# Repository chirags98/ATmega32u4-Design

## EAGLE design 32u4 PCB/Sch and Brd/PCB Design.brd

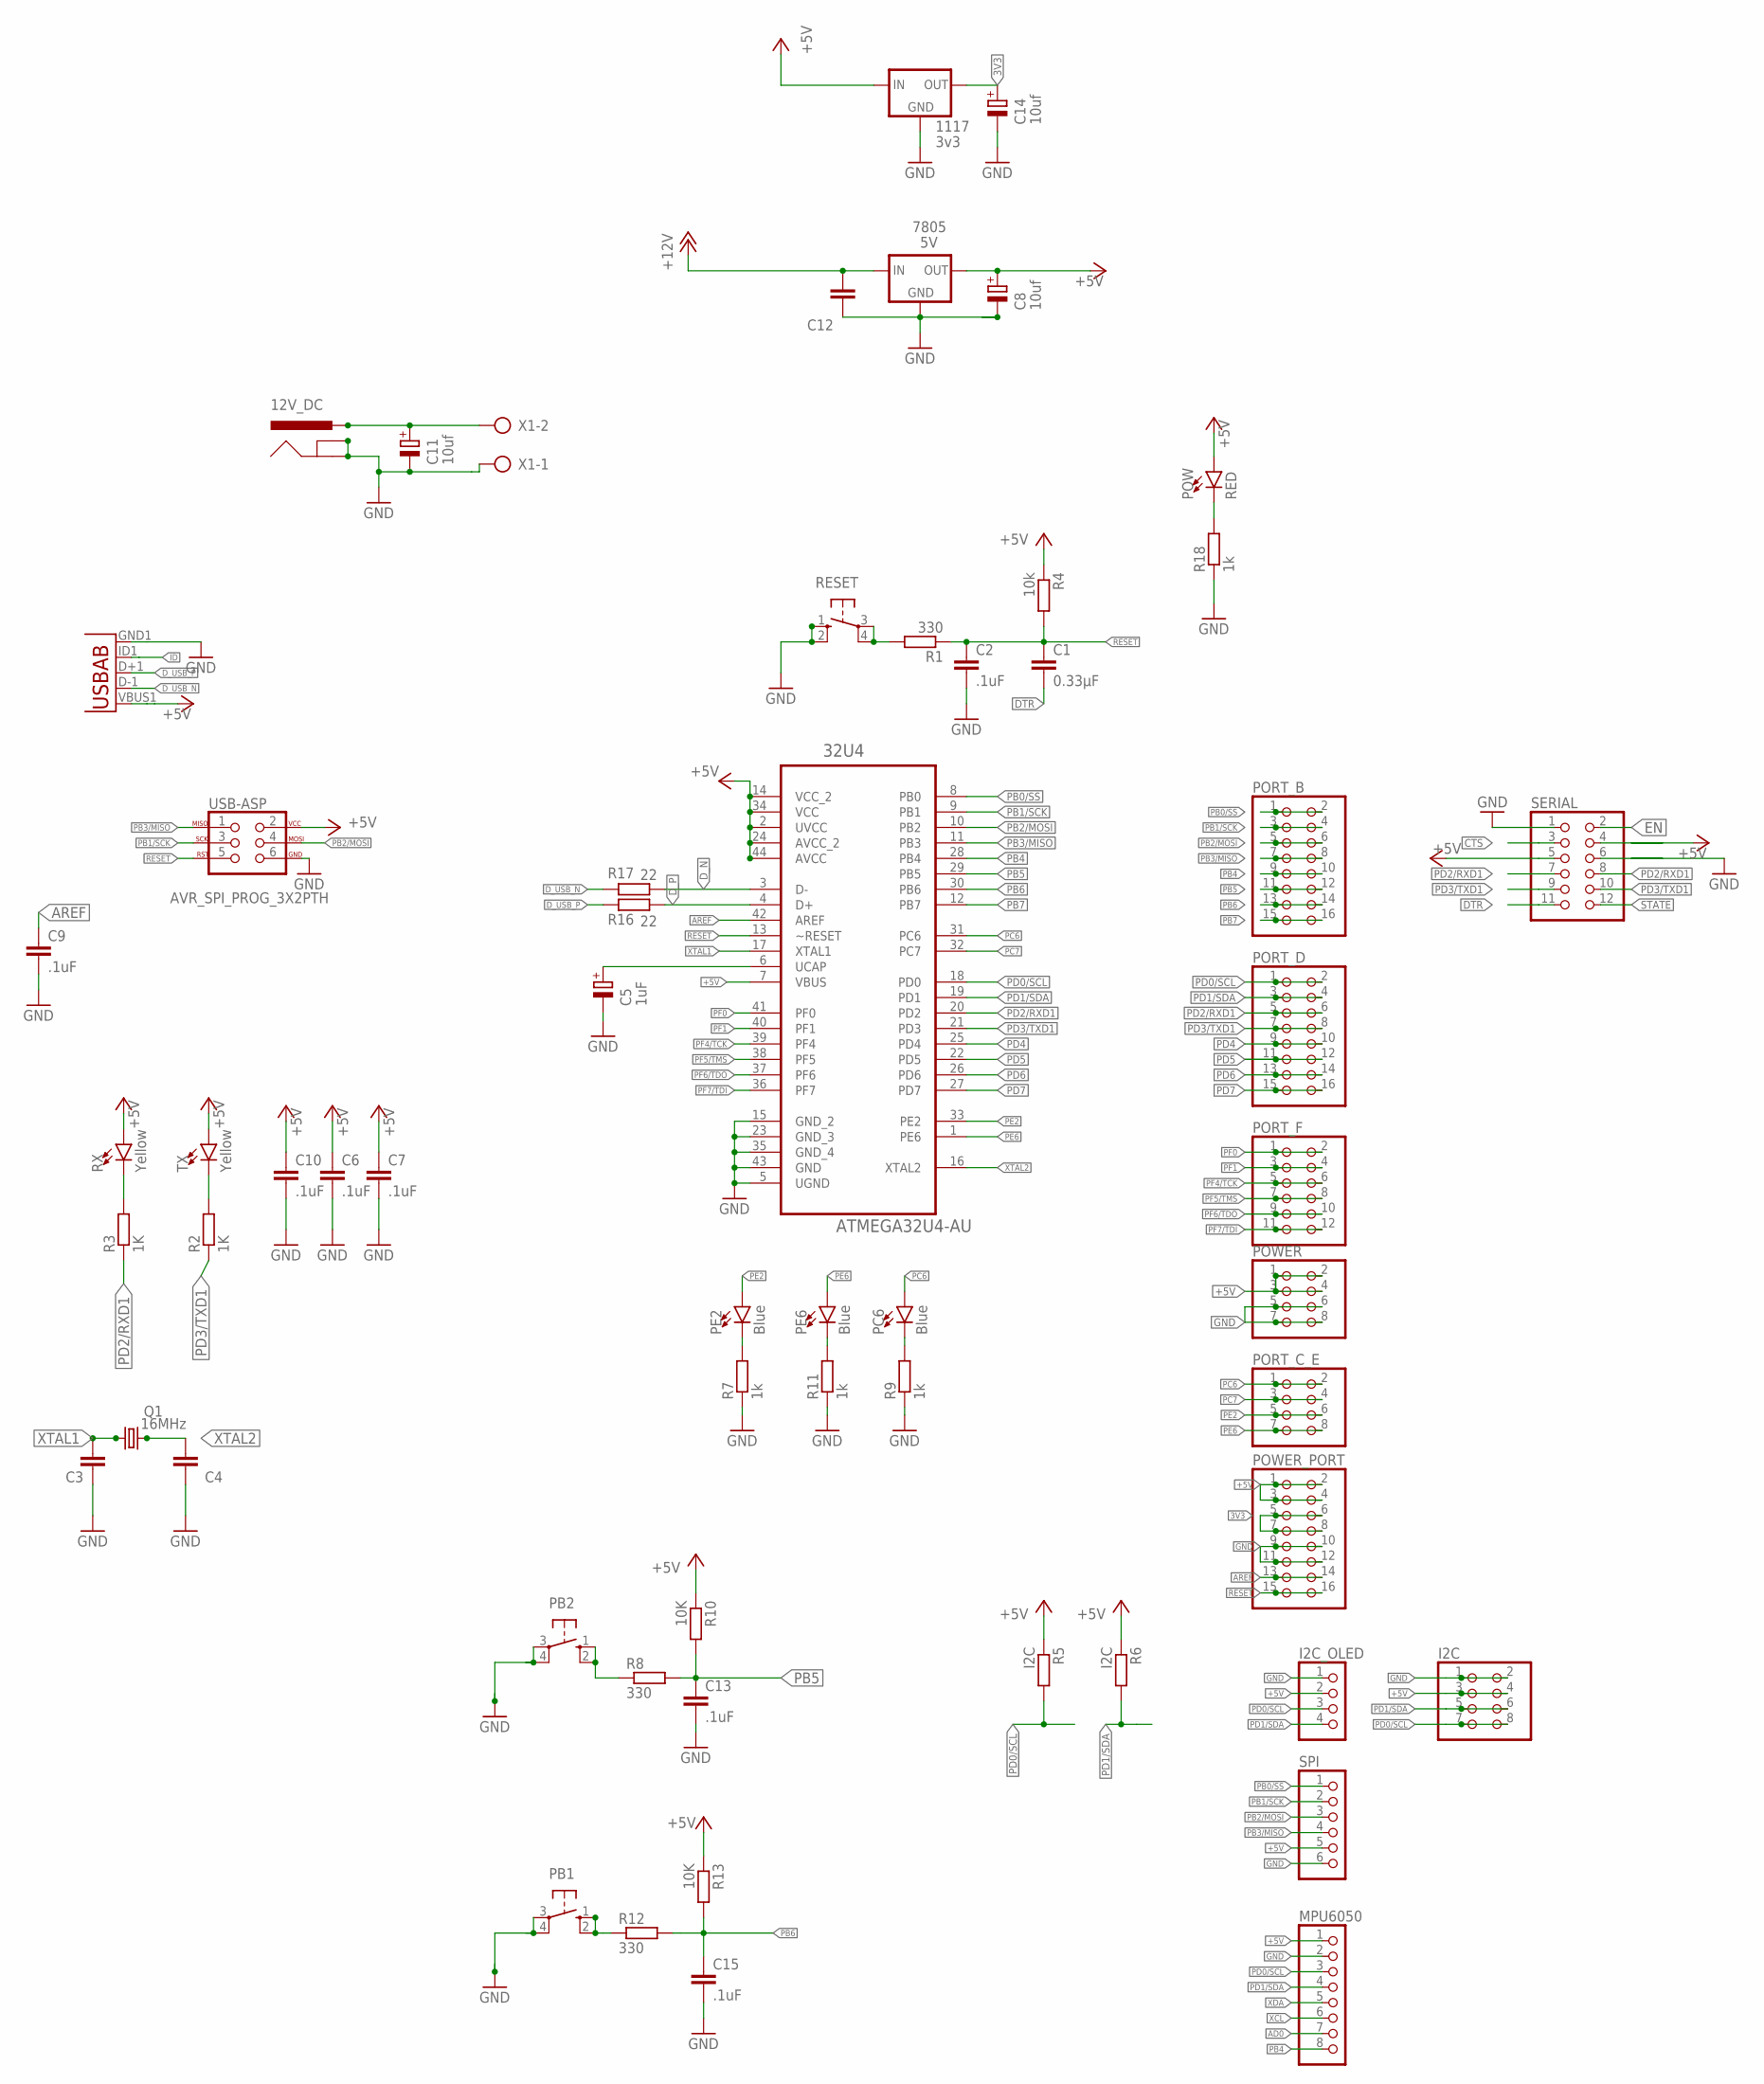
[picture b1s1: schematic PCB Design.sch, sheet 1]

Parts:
12V_DC: POWER_JACK; POWER_JACK_PTH; MPN SPC21365
32U4: ATMEGA32U4-AU; QFP80P1200X1200X120-44N
1117: 3v3; SOT223
7805: 5V; TO-252
C1: 0.33µF; C0805K
C2, C6, C7, C9, C10, C13, C15: .1uF; C0805K
C3, C4: 22pF; C0805K
C5: 1uF; E2,5-6
C8, C11, C14: 10uf; E2,5-6
C12: .1uf; C0805K
I2C: PINHD-2X4; 2X04
I2C_OLED: PINHD-1X4; 1X04
MPU6050: PINHD-1X8; 1X08
PB1, PB2: 10-XX; B3F-10XX
PC6: Blue; LED-0603
PE2, PE6: Blue; LED-0603
PORT_B: PINHD-2X8; 2X08
PORT_C_E: PINHD-2X4; 2X04
PORT_D: PINHD-2X8; 2X08
PORT_F: PINHD-2X6; 2X06
POW: RED; LED-0603
POWER: PINHD-2X4; 2X04
POWER_PORT: PINHD-2X8; 2X08
Q1: 16MHz; HC49U70
R1, R8, R12: 330; M0805
R2, R3: 1K; M0805
R4: 10k; M0805
R5, R6: I2C; M0805
R7, R9, R11, R18: 1k; M0805
R10, R13: 10K; M0805
R16, R17: 22; M0805
RESET: 10-XX; B3F-10XX
RX: Yellow; LED-0603
SERIAL: PINHD-2X6; 2X06
SPI: PINHD-1X6; 1X06
TX: Yellow; LED-0603
U1: USB""; USB-MICRO-SMD
USB-ASP: AVR_SPI_PROG_3X2PTH; 2X3
X1: AK500/2-H

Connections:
3V3: 1117.2 (OUT), C14.+, POWER_PORT.5, POWER_PORT.6, POWER_PORT.7, POWER_PORT.8
+5V: 32U4.2 (UVCC), 32U4.7 (VBUS), 32U4.14 (VCC_2), 32U4.24 (AVCC_2), 32U4.34 (VCC), 32U4.44 (AVCC), 1117.3 (IN), 7805.2 (OUT), C6.1, C7.1, C8.+, C10.1, I2C.3, I2C.4, I2C_OLED.2, MPU6050.1, POW.A, POWER.1, POWER.2, POWER.3, POWER.4, POWER_PORT.1, POWER_PORT.2, POWER_PORT.3, POWER_PORT.4, R4.1, R5.1, R6.1, R10.1, R13.1, RX.A, SERIAL.4, SERIAL.5, SPI.5, TX.A, U1.VBUS1 (VBUS), USB-ASP.2; also elsewhere on the board
+12V: 12V_DC.PWR, 7805.1 (IN), C11.+, C12.1, X1.2
AD0: MPU6050.7
AREF: 32U4.42 (AREF), C9.1, POWER_PORT.13, POWER_PORT.14
CTS: SERIAL.3
DTR: C1.2, SERIAL.11
D_N: 32U4.3 (D-), R17.1
D_P: 32U4.4 (D+), R16.1
D_USB_N: R17.2, U1.D-1 (D-)
D_USB_P: R16.2, U1.D+1 (D+)
EN: SERIAL.2
GND: 12V_DC.GND, 12V_DC.GNDBREAK, 32U4.5 (UGND), 32U4.15 (GND_2), 32U4.23 (GND_3), 32U4.35 (GND_4), 32U4.43 (GND), 1117.1 (GND), 7805.3 (GND), C2.2, C3.1, C4.1, C5.-, C6.2, C7.2, C8.-, C9.2, C10.2, C11.-, C12.2, C13.2, C14.-, C15.2, I2C.1, I2C.2, I2C_OLED.1, MPU6050.2, PB1.3, PB1.4 (P1), PB2.3, PB2.4 (P1), POWER.5, POWER.6, POWER.7, POWER.8, POWER_PORT.9, POWER_PORT.10, POWER_PORT.11, POWER_PORT.12, R7.1, R9.1, R11.1, R18.1, RESET.1 (S), RESET.2 (S1), SERIAL.1, SERIAL.6, SPI.6, U1.GND1 (GND), USB-ASP.6, X1.1; also elsewhere on the board
ID: U1.ID1 (USBID)
unnamed: PC6.C, R9.2
unnamed: POW.C, R18.2
unnamed: PE6.C, R11.2
unnamed: PE2.C, R7.2
unnamed: R2.2, TX.C
unnamed: R3.2, RX.C
unnamed: R1.2, RESET.3, RESET.4 (P1)
unnamed: PB1.1 (S), PB1.2 (S1), R12.1
unnamed: PB2.1 (S), PB2.2 (S1), R8.1
unnamed: 32U4.6 (UCAP), C5.+
PB0/SS: 32U4.8 (PB0), PORT_B.1, PORT_B.2, SPI.1
PB1/SCK: 32U4.9 (PB1), PORT_B.3, PORT_B.4, SPI.2, USB-ASP.3
PB2/MOSI: 32U4.10 (PB2), PORT_B.5, PORT_B.6, SPI.3, USB-ASP.4
PB3/MISO: 32U4.11 (PB3), PORT_B.7, PORT_B.8, SPI.4, USB-ASP.1
PB4: 32U4.28 (PB4), MPU6050.8, PORT_B.9, PORT_B.10
PB5: 32U4.29 (PB5), C13.1, PORT_B.11, PORT_B.12, R8.2, R10.2
PB6: 32U4.30 (PB6), C15.1, PORT_B.13, PORT_B.14, R12.2, R13.2
PB7: 32U4.12 (PB7), PORT_B.15, PORT_B.16
PC6: 32U4.31 (PC6), PC6.A, PORT_C_E.1, PORT_C_E.2
PC7: 32U4.32 (PC7), PORT_C_E.3, PORT_C_E.4
PD0/SCL: 32U4.18 (PD0), I2C.7, I2C.8, I2C_OLED.3, MPU6050.3, PORT_D.1, PORT_D.2, R5.2
PD1/SDA: 32U4.19 (PD1), I2C.5, I2C.6, I2C_OLED.4, MPU6050.4, PORT_D.3, PORT_D.4, R6.2
PD2/RXD1: 32U4.20 (PD2), PORT_D.5, PORT_D.6, R3.1, SERIAL.7, SERIAL.8
PD3/TXD1: 32U4.21 (PD3), PORT_D.7, PORT_D.8, R2.1, SERIAL.9, SERIAL.10
PD4: 32U4.25 (PD4), PORT_D.9, PORT_D.10
PD5: 32U4.22 (PD5), PORT_D.11, PORT_D.12
PD6: 32U4.26 (PD6), PORT_D.13, PORT_D.14
PD7: 32U4.27 (PD7), PORT_D.15, PORT_D.16
PE2: 32U4.33 (PE2), PE2.A, PORT_C_E.5, PORT_C_E.6
PE6: 32U4.1 (PE6), PE6.A, PORT_C_E.7, PORT_C_E.8
PF0: 32U4.41 (PF0), PORT_F.1, PORT_F.2; also elsewhere on the board
PF1: 32U4.40 (PF1), PORT_F.3, PORT_F.4; also elsewhere on the board
PF4/TCK: 32U4.39 (PF4), PORT_F.5, PORT_F.6; also elsewhere on the board
PF5/TMS: 32U4.38 (PF5), PORT_F.7, PORT_F.8; also elsewhere on the board
PF6/TDO: 32U4.37 (PF6), PORT_F.9, PORT_F.10; also elsewhere on the board
PF7/TDI: 32U4.36 (PF7), PORT_F.11, PORT_F.12; also elsewhere on the board
RESET: 32U4.13 (~RESET), C1.1, C2.1, POWER_PORT.15, POWER_PORT.16, R1.1, R4.2, USB-ASP.5
STATE: SERIAL.12
XCL: MPU6050.6
XDA: MPU6050.5
XTAL1: 32U4.17 (XTAL1), C3.2, Q1.1
XTAL2: 32U4.16 (XTAL2), C4.2, Q1.2

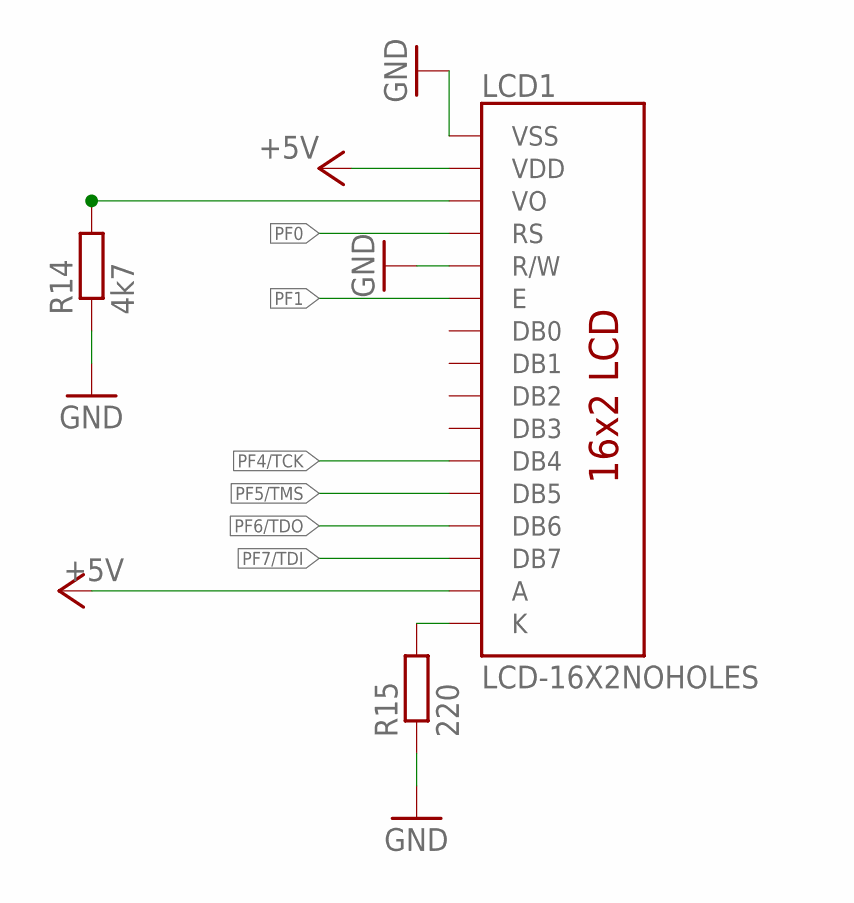
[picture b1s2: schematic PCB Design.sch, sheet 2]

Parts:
LCD1: LCD-16X2NOHOLES; LCD-16X2_NOHOLESNOSILK
R14: 4k7; M0805
R15: 220; M0805

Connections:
+5V: LCD1.2 (VDD), LCD1.15 (A); also elsewhere on the board
GND: LCD1.1 (VSS), LCD1.5 (R/W), R14.1, R15.1; also elsewhere on the board
unnamed: LCD1.3 (VO), R14.2
unnamed: LCD1.16 (K), R15.2
PF0: LCD1.4 (RS); also elsewhere on the board
PF1: LCD1.6 (E); also elsewhere on the board
PF4/TCK: LCD1.11 (DB4); also elsewhere on the board
PF5/TMS: LCD1.12 (DB5); also elsewhere on the board
PF6/TDO: LCD1.13 (DB6); also elsewhere on the board
PF7/TDI: LCD1.14 (DB7); also elsewhere on the board

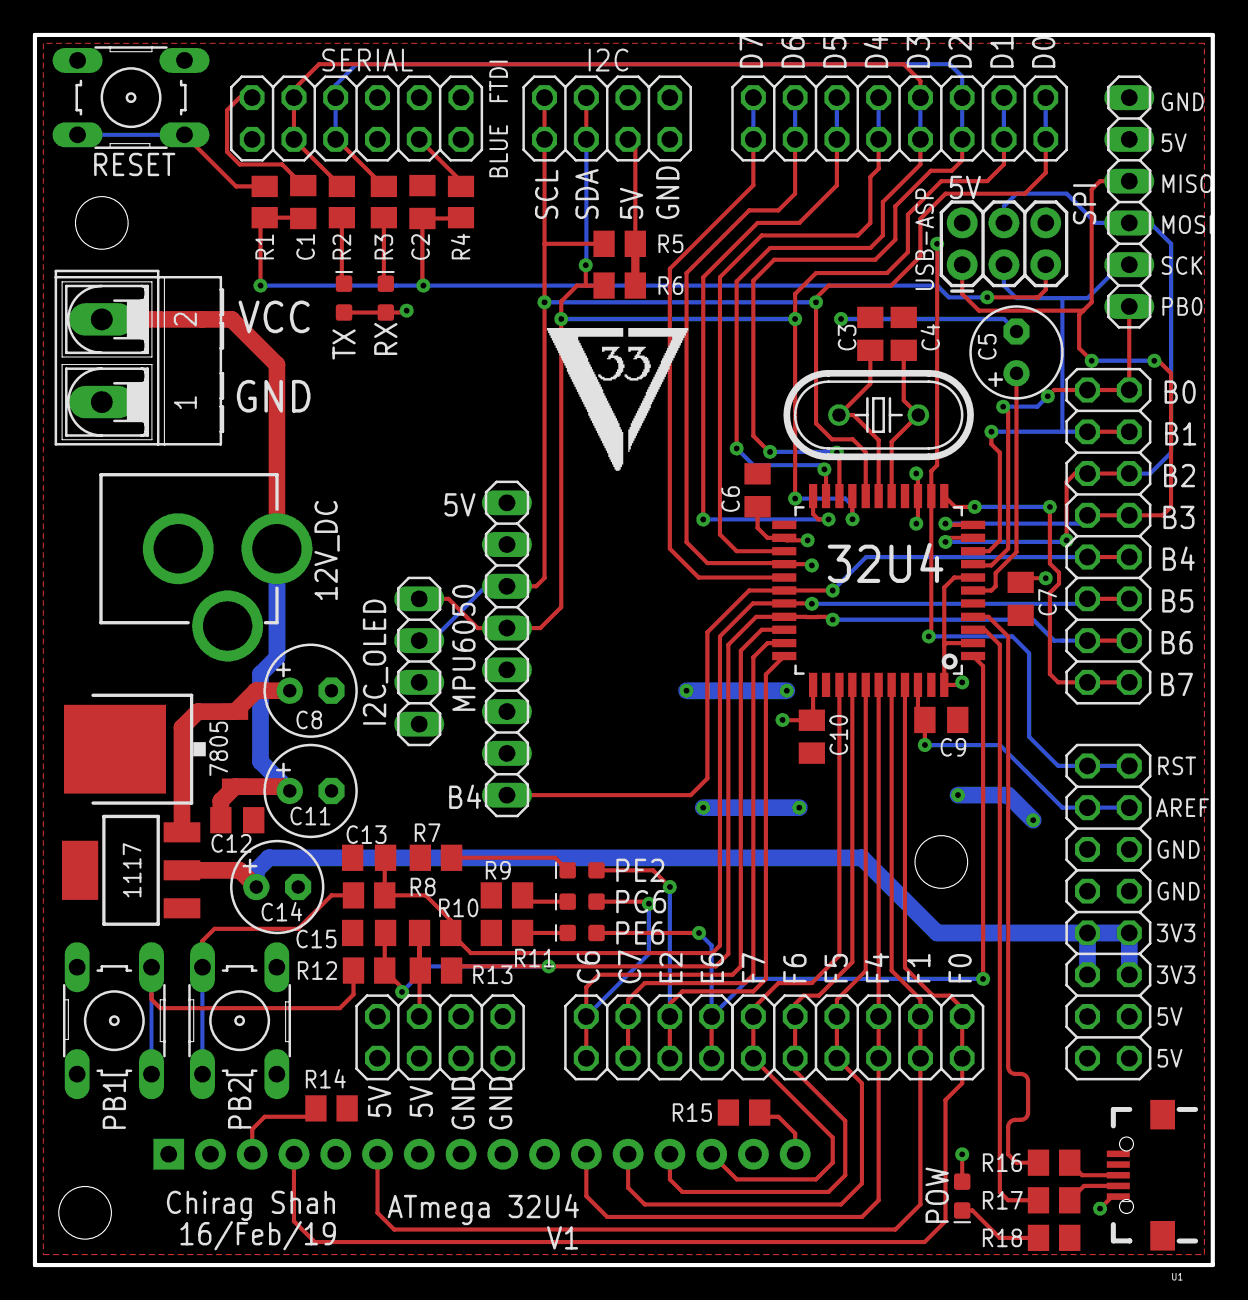
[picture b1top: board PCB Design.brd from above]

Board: 2 copper layers, 71.6 x 74.8 mm, 62 parts (0 on the bottom side), 51 nets.

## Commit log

2019-01-01 Initial Commit - Working on schematic
2019-01-06 Started routinng
2019-01-09 Rough layout ready
2019-01-15 Routing almost done
2019-01-20 Routing done - Awiiting verification
2019-01-27 Adjusted Silkscreen, added bluetooth
2019-02-16 Manufacture
2019-02-16 New Manufacture, first one scrapped
2019-03-15 Changed values and modified BOM
2019-03-16 Changed Silkscreen

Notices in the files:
parts and their libraries:
SparkFun-Connectors: Licensing: Creative Commons ShareAlike 4.0 International - https://creativecommons.org/licenses/by-sa/4.0
